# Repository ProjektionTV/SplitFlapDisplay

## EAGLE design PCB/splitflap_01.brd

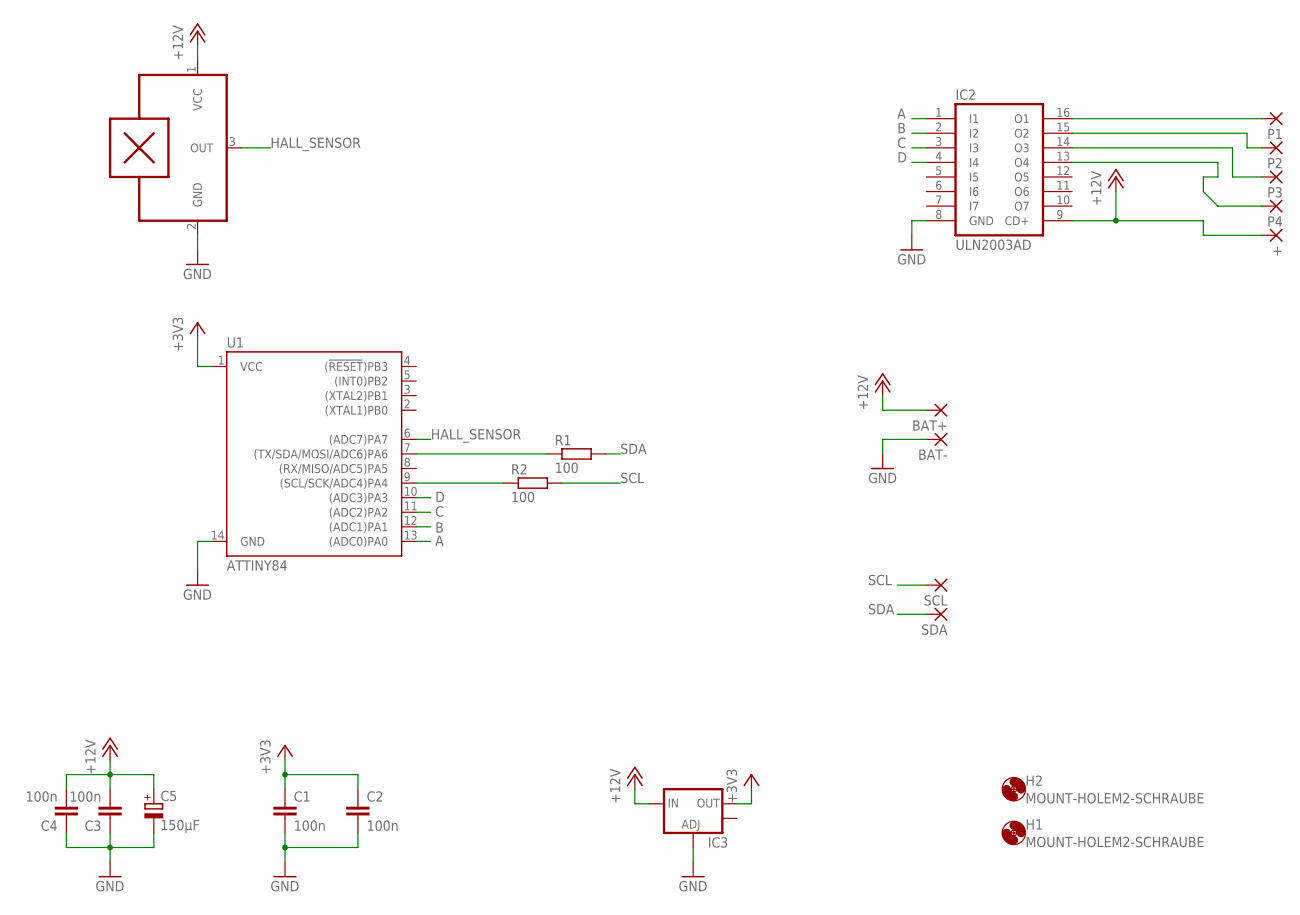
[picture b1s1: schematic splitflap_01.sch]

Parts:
+: SMD5; SMD2,54-5,08
BAT+: SMD5; SMD2,54-5,08
BAT-: SMD5; SMD2,54-5,08
C1, C2, C3, C4: 100n; C0805
C5: 150µF; SMC_D
H1, H2: MOUNT-HOLEM2-SCHRAUBE; M2-SCHRAUBE
IC2: ULN2003AD; SO16
IC3: V_REG_LM1117SOT223; SOT223
P1, P2, P3, P4: SMD5; SMD2,54-5,08
R1, R2: 100; R0805
SCL: SMD5; SMD2,54-5,08
SDA: SMD5; SMD2,54-5,08
U1: ATTINY84; SO14
U$1: A3144; TO-92-LINE

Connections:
+3V3: C1.1, C2.1, IC3.2 (OUT), U1.1 (VCC)
+12V: +.1, BAT+.1, C3.2, C4.2, C5.+, IC2.9 (CD+), IC3.3 (IN), U$1.1 (VCC)
A: IC2.1 (I1), U1.13 ((ADC0)PA0)
B: IC2.2 (I2), U1.12 ((ADC1)PA1)
C: IC2.3 (I3), U1.11 ((ADC2)PA2)
D: IC2.4 (I4), U1.10 ((ADC3)PA3)
GND: BAT-.1, C1.2, C2.2, C3.1, C4.1, C5.-, IC2.8 (GND), IC3.1 (ADJ), U1.14 (GND), U$1.2 (GND)
HALL_SENSOR: U1.6 ((ADC7)PA7), U$1.3 (OUT)
unnamed: R1.1, U1.7 ((TX/SDA/MOSI/ADC6)PA6)
unnamed: R2.1, U1.9 ((SCL/SCK/ADC4)PA4)
unnamed: IC2.16 (O1), P1.1
unnamed: IC2.15 (O2), P2.1
unnamed: IC2.14 (O3), P3.1
unnamed: IC2.13 (O4), P4.1
SCL: R2.2, SCL.1
SDA: R1.2, SDA.1

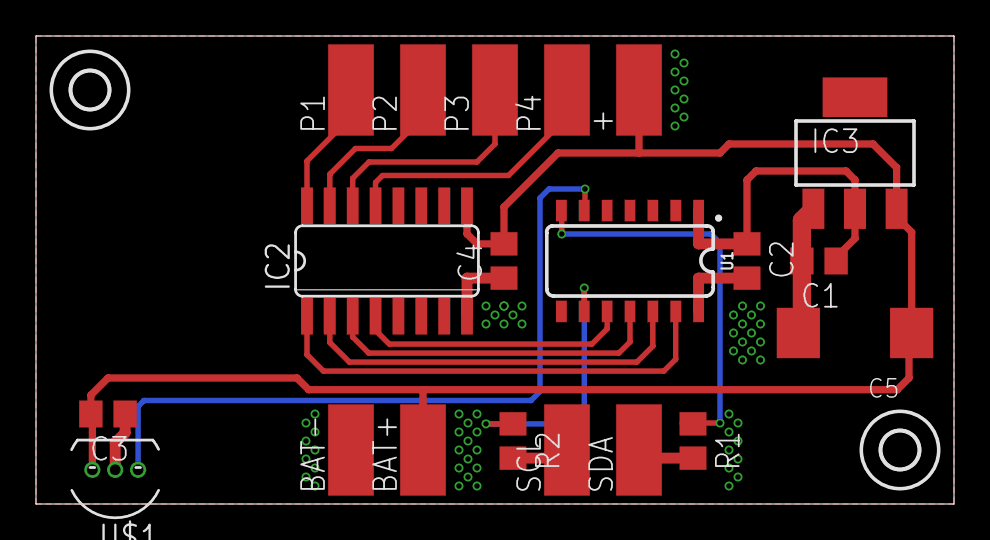
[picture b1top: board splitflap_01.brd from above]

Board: 2 copper layers, 51.0 x 26.0 mm, 22 parts (0 on the bottom side), 16 nets.

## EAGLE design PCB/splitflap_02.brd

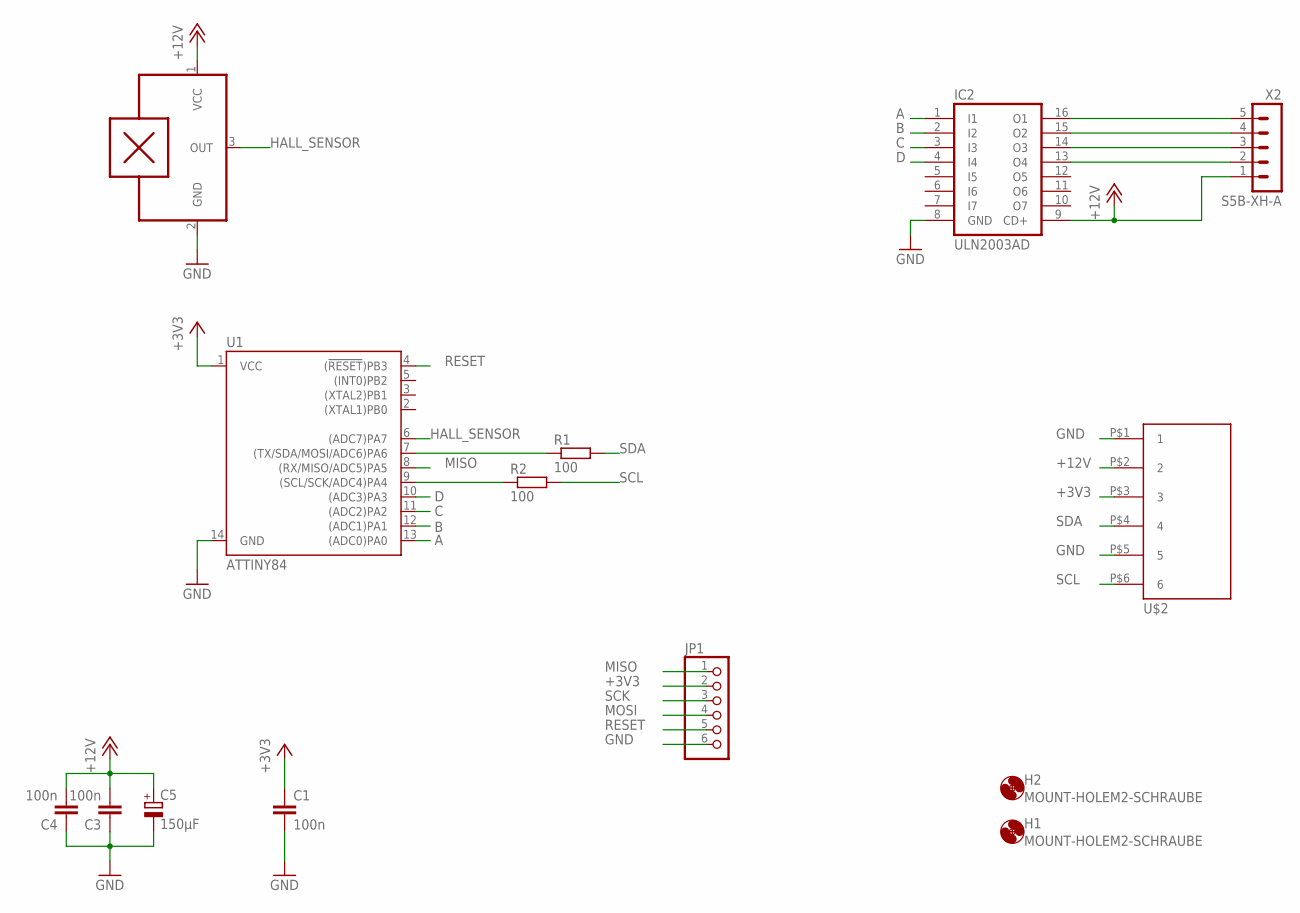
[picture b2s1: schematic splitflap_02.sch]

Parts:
C1, C3, C4: 100n; C0805
C5: 150µF; SMC_D
H1, H2: MOUNT-HOLEM2-SCHRAUBE; M2-SCHRAUBE
IC2: ULN2003AD; SO16
JP1: PINHD-1X6M; 1X06M
R1, R2: 100; R0805
U1: ATTINY84; SO14
U$1: A3144; TO-92-LINE
U$2: AMP-MICROMATCH-06
X2: S5B-XH-A

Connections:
+3V3: C1.1, JP1.2, U1.1 (VCC), U$2.P$3 (3)
+12V: C3.2, C4.2, C5.+, IC2.9 (CD+), U$1.1 (VCC), U$2.P$2 (2), X2.1
A: IC2.1 (I1), U1.13 ((ADC0)PA0)
B: IC2.2 (I2), U1.12 ((ADC1)PA1)
C: IC2.3 (I3), U1.11 ((ADC2)PA2)
D: IC2.4 (I4), U1.10 ((ADC3)PA3)
GND: C1.2, C3.1, C4.1, C5.-, IC2.8 (GND), JP1.6, U1.14 (GND), U$1.2 (GND), U$2.P$1 (1), U$2.P$5 (5)
HALL_SENSOR: U1.6 ((ADC7)PA7), U$1.3 (OUT)
MISO: JP1.1, U1.8 ((RX/MISO/ADC5)PA5)
MOSI: JP1.4, R1.1, U1.7 ((TX/SDA/MOSI/ADC6)PA6)
unnamed: IC2.16 (O1), X2.5
unnamed: IC2.15 (O2), X2.4
unnamed: IC2.14 (O3), X2.3
unnamed: IC2.13 (O4), X2.2
RESET: JP1.5, U1.4 ((!RESET!)PB3)
SCK: JP1.3, R2.1, U1.9 ((SCL/SCK/ADC4)PA4)
SCL: R2.2, U$2.P$6 (6)
SDA: R1.2, U$2.P$4 (4)

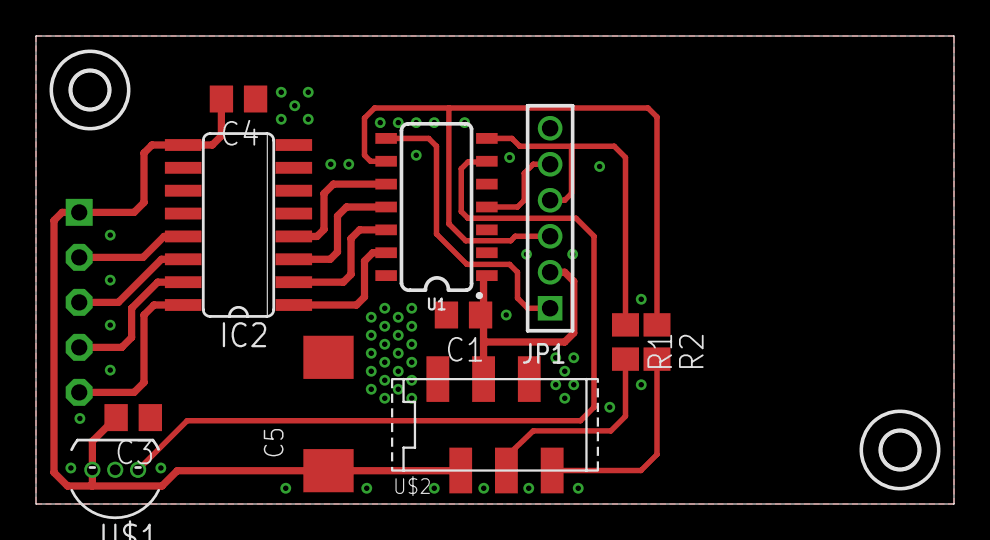
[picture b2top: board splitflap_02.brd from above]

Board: 2 copper layers, 51.0 x 26.0 mm, 14 parts (1 on the bottom side), 18 nets.

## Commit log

2021-09-13 FileCopy
2021-09-13 1. Vorschlag by happyprinter
2021-09-14 2. Version by Happyprinter
2021-09-20 neue Version für HP
2021-09-21 Schön layoutete Version by Happyprinter

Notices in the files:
parts and their libraries:
SparkFun-IC-Microcontroller: Licensing: Creative Commons ShareAlike 4.0 International - https://creativecommons.org/licenses/by-sa/4.0
